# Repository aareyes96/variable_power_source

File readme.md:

# Variable Power Source

An essential tool in an electronics workshop is a Variable Power Source. This must regulate current and voltage delivered in addition to having protections against short circuits.

This Variable Power Supply is built by modifying an old PC ATX power supply and based on a tutorial made by Cuban electronics [here](http://cubaelectronica.blogspot.com/2017/06/hacer-fuente-atx-pc-variable-desde-1-28.html) where the modifications that need to be made to the PC ATX Power Supply are explained.

>### _**Here the microcontroller control board is made to achieve better control precision. It also provides a real-time current, voltage and power measurement.**_

## Features

* Complete range ( from 0V to 30V and 0A to 15A ) control with a maximum precision for a wide range.
* Fast short-circuit protection.
* Minimum modifications made to ATX Power Supply.
* Nice and clear interface.
* ~~5V (of Standby supply) for USB plug~~ (Not supported yet).
* small design (all into ATX chassis) by choice.

## What do you need ?

* Bluepill (STM32F103C8T6 microcontroller based board).
* OLED 128x64 0.96"(SSD1306 based)  ~~display or LCD 16x2 Display~~(Actually not supported).
* A rotary encoder with central Button.
* LM324 IC.
* BD139 Transistor.
* Some others common components (Resistors and Capacitors, LEDs, Connectors, a little switch, etc).

## Softwares Used

* STM32CubeIDE 1.3.0 (Firmware and Debug).
* KiCAD (Schematic and PCB).
* NI Multisim 14.0 (Simulations).

## **Important Note**

>PCB layout is made to do at home (DIY). They are not optimized to manufacture with a PCB manufacturing company like JLCPCB or others.

## Preview

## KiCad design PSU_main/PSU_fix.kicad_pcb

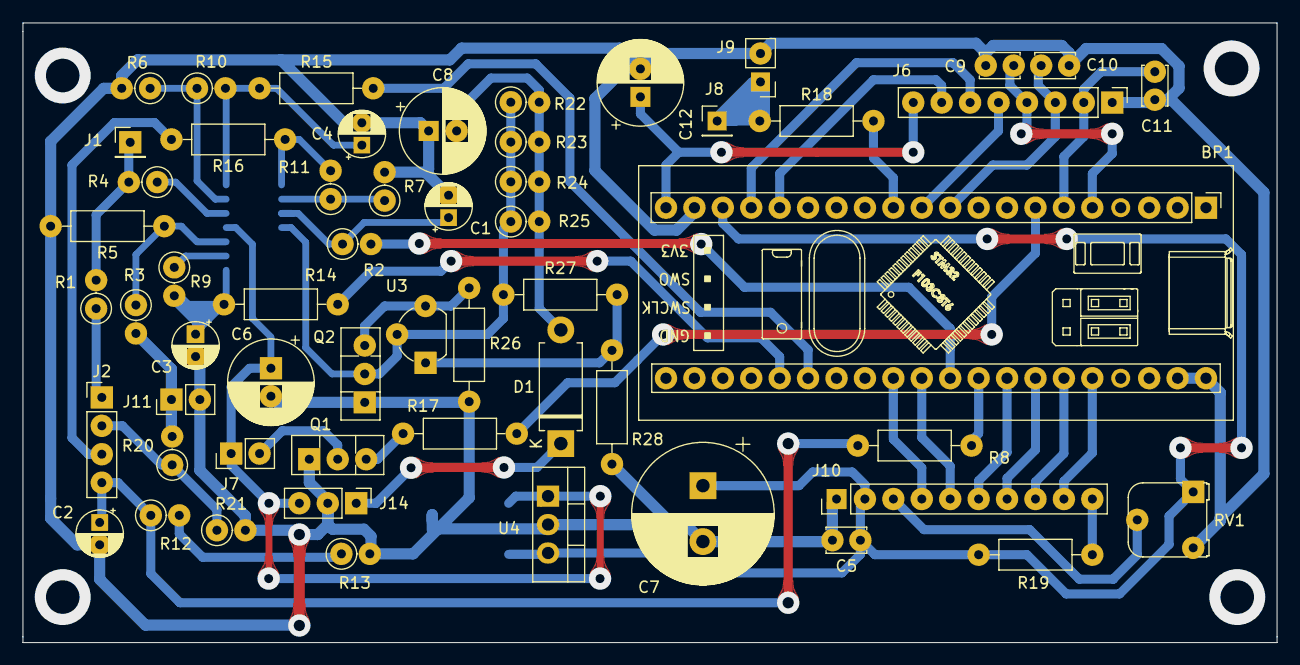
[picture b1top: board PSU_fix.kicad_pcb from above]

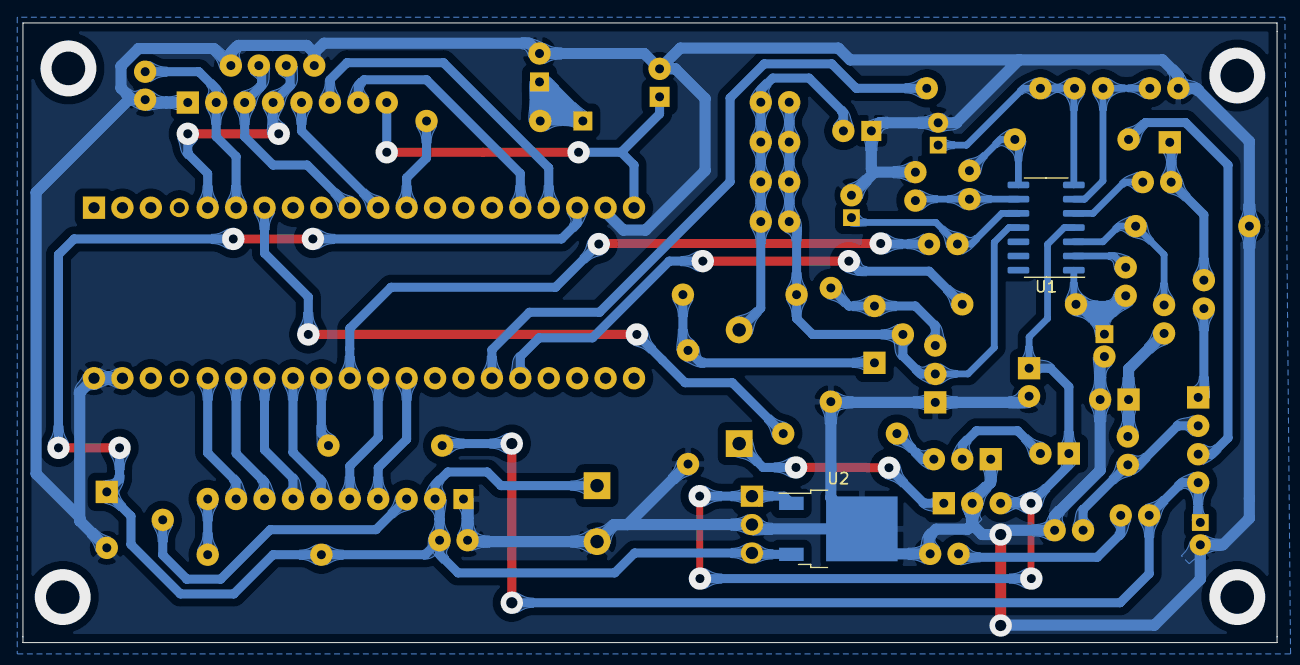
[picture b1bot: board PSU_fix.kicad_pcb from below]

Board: 2 copper layers, 112.1 x 55.4 mm, 58 parts (2 on the bottom side), 48 nets.

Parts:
BP1: BluePill_1; YAAJ_BluePill_1
C1, C2, C3, C4: 10u; CP_Radial_D4.0mm_P2.00mm
C5, C9, C10, C11: 100n; C_Disc_D3.4mm_W2.1mm_P2.50mm
C6, C8, C12: 100u; CP_Radial_D7.5mm_P2.50mm
C7: 4700u; CP_Radial_D12.5mm_P5.00mm
D1: D_Schottky; D_DO-15_P10.16mm_Horizontal
J1: RSHUNT; PinHeader_1x01_P2.54mm_Vertical
J2: TL494; PinHeader_1x04_P2.54mm_Vertical
J6: OLED; PinHeader_1x08_P2.54mm_Vertical
J7: PSU FAN; PinHeader_1x02_P2.54mm_Vertical
J8: PS_ON; PinHeader_1x01_P2.54mm_Vertical
J9: SW_STBY; PinHeader_1x02_P2.54mm_Vertical
J10: LCD 16x2; PinHeader_1x10_P2.54mm_Vertical
J11: Conn_01x02; PinHeader_1x02_P2.54mm_Vertical
J14: 12_SIMETRICOS; PinHeader_1x03_P2.54mm_Vertical
Q1: BD139; TO-126-3_Vertical
Q2: BD138; TO-126-3_Vertical
R1, R2, R4, R21: 2K; R_Axial_DIN0207_L6.3mm_D2.5mm_P2.54mm_Vertical
R3: 22k; R_Axial_DIN0207_L6.3mm_D2.5mm_P2.54mm_Vertical
R5: 2k; R_Axial_DIN0207_L6.3mm_D2.5mm_P10.16mm_Horizontal
R6, R9, R20: 10K; R_Axial_DIN0207_L6.3mm_D2.5mm_P2.54mm_Vertical
R7: 5.1K; R_Axial_DIN0207_L6.3mm_D2.5mm_P2.54mm_Vertical
R8, R16, R18: 2K; R_Axial_DIN0207_L6.3mm_D2.5mm_P10.16mm_Horizontal
R10: 20K; R_Axial_DIN0207_L6.3mm_D2.5mm_P2.54mm_Vertical
R11: 2.7K; R_Axial_DIN0207_L6.3mm_D2.5mm_P2.54mm_Vertical
R12: 220; R_Axial_DIN0207_L6.3mm_D2.5mm_P2.54mm_Vertical
R13: 150; R_Axial_DIN0207_L6.3mm_D2.5mm_P2.54mm_Vertical
R14, R15: 220; R_Axial_DIN0207_L6.3mm_D2.5mm_P10.16mm_Horizontal
R17: 1K; R_Axial_DIN0207_L6.3mm_D2.5mm_P10.16mm_Horizontal
R19: 100; R_Axial_DIN0207_L6.3mm_D2.5mm_P10.16mm_Horizontal
R22, R23, R24, R25: 4.7K; R_Axial_DIN0207_L6.3mm_D2.5mm_P2.54mm_Vertical
R26, R27: 2.2k; R_Axial_DIN0207_L6.3mm_D2.5mm_P10.16mm_Horizontal
R28: 8.2k; R_Axial_DIN0207_L6.3mm_D2.5mm_P10.16mm_Horizontal
RV1: 10K; Potentiometer_Runtron_RM-065_Vertical
U1: LM324; SOIC-14_3.9x8.7mm_P1.27mm
U2: L7805; TO-252-2
U3: TL431LP; TO-92_Wide
U4: L7805; TO-220-3_Vertical

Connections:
+5V: BP1.18, C5.1, C7.1, J10.2, R19.1, RV1.1, U2.3, U4.3
+12V: C6.1, J7.1, J14.3, U1.4, U2.1, U4.1
-12V: Q2.2, R22.1, R23.1, R24.1, R25.1, R27.1, U1.11, U3.2
/PIN_1_TL494: J2.2, R20.1, R21.1
/PIN_2_TL494: J2.3, R16.2
/PIN_15_TL494: C2.1, J2.4, R8.1, R12.1
/PIN_16_TL494: J2.1, R1.1
A0: BP1.25, R14.2
A1: BP1.26, R15.2
A6: BP1.31, R2.2
A7: BP1.32, R8.2
A10: BP1.7, R17.2
B4: BP1.12, R18.2
GND: BP1.19, BP1.39, BP1.40, C1.2, C2.2, C3.2, C4.2, C5.2, C6.2, C7.2, C8.1, C9.1, C10.2, C11.1, C12.2, J6.1, J9.2, J10.1, J11.2, J14.2, Q1.1, Q2.1, R5.2, R6.2, R7.2, R13.2, R21.2, R26.2, R28.2, RV1.3, U2.2, U4.2
unnamed: BP1.5, C9.2, J6.4
unnamed: BP1.6, C11.2, J6.2
unnamed: BP1.10, C10.1, J6.3
unnamed: BP1.11, J6.5
unnamed: BP1.16, J6.7
unnamed: BP1.17, J6.6
unnamed: BP1.20, C12.1, J6.8
unnamed: BP1.29, J10.4
unnamed: BP1.30, J10.5
unnamed: BP1.33, J10.6
unnamed: BP1.34, J10.7
unnamed: BP1.35, J10.8
unnamed: BP1.36, J10.9
unnamed: C1.1, R2.1, U1.10
unnamed: C3.1, R9.2, R14.1, U1.1
unnamed: C4.1, R10.2, R15.1, U1.7
unnamed: C8.2, D1.2, R22.2, R23.2, R24.2, R25.2
unnamed: D1.1, J14.1
unnamed: J1.1, R1.2, R4.2
unnamed: J7.2, Q1.2
unnamed: J8.1, J9.1, R18.1
unnamed: J10.3, RV1.2
unnamed: J10.10, R19.2
unnamed: Q1.3, R17.1
unnamed: Q2.3, R26.1, U3.3
unnamed: R3.1, R5.1, U1.3
unnamed: R4.1, U1.5
unnamed: R9.1, U1.2
unnamed: R6.1, R10.1, U1.6
unnamed: R7.1, R11.1, U1.9
unnamed: R11.2, R16.1, U1.8
unnamed: R12.2, R13.1
unnamed: R27.2, R28.1, U3.1
Vout: J11.1, R3.2, R20.2

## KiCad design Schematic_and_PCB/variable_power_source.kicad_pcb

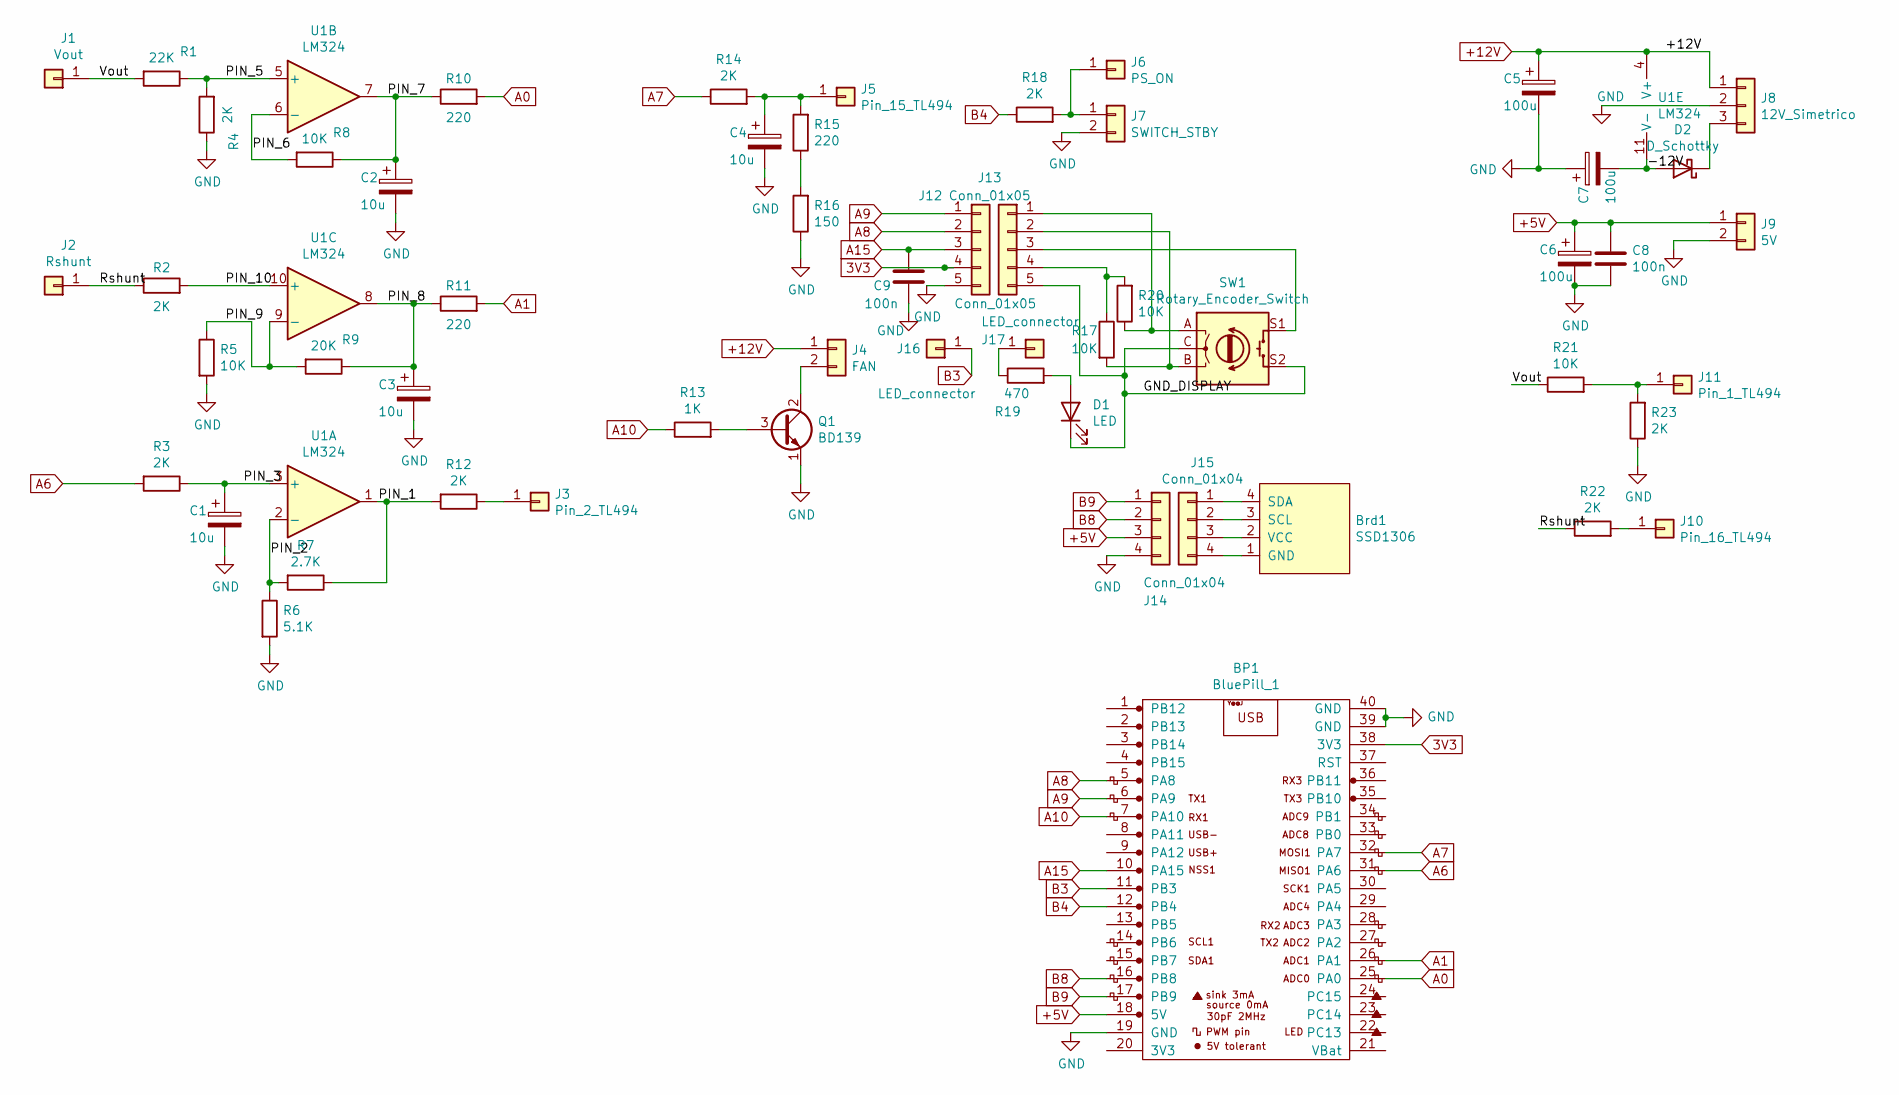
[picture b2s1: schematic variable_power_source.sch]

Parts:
BP1: BluePill_1; YAAJ_BluePill
Brd1: SSD1306; 128x64OLED
C1, C2, C3, C4: 10u; CP_Radial_D4.0mm_P2.00mm
C5, C6, C7: 100u; CP_Radial_D8.0mm_P2.50mm
C8, C9: 100n; C_Disc_D4.3mm_W1.9mm_P5.00mm
D1: LED; LED_D5.0mm
D2: D_Schottky; D_DO-41_SOD81_P10.16mm_Horizontal
J1: Vout; PinHeader_1x01_P2.54mm_Vertical
J2: Rshunt; PinHeader_1x01_P2.54mm_Vertical
J3: Pin_2_TL494; PinHeader_1x01_P2.54mm_Vertical
J4: FAN; PinHeader_1x02_P2.54mm_Vertical
J5: Pin_15_TL494; PinHeader_1x01_P2.54mm_Vertical
J6: PS_ON; PinHeader_1x01_P2.54mm_Vertical
J7: SWITCH_STBY; PinHeader_1x02_P2.54mm_Vertical
J8: 12V_Simetrico; PinHeader_1x03_P2.54mm_Vertical
J9: 5V; PinHeader_1x02_P2.54mm_Vertical
J10: Pin_16_TL494; PinHeader_1x01_P2.54mm_Vertical
J11: Pin_1_TL494; PinHeader_1x01_P2.54mm_Vertical
J12, J13: Conn_01x05; PinHeader_1x05_P2.54mm_Vertical
J14, J15: Conn_01x04; PinHeader_1x04_P2.54mm_Vertical
J16, J17: LED_connector; PinHeader_1x01_P2.54mm_Vertical
Q1: BD139; TO-126-3_Vertical
R1: 22K; R_Axial_DIN0207_L6.3mm_D2.5mm_P2.54mm_Vertical
R2, R3, R4, R12, R14, R18, R22, R23: 2K; R_Axial_DIN0207_L6.3mm_D2.5mm_P2.54mm_Vertical
R5, R8, R17, R20, R21: 10K; R_Axial_DIN0207_L6.3mm_D2.5mm_P2.54mm_Vertical
R6: 5.1K; R_Axial_DIN0207_L6.3mm_D2.5mm_P2.54mm_Vertical
R7: 2.7K; R_Axial_DIN0207_L6.3mm_D2.5mm_P2.54mm_Vertical
R9: 20K; R_Axial_DIN0207_L6.3mm_D2.5mm_P2.54mm_Vertical
R10, R11, R15: 220; R_Axial_DIN0207_L6.3mm_D2.5mm_P2.54mm_Vertical
R13: 1K; R_Axial_DIN0207_L6.3mm_D2.5mm_P2.54mm_Vertical
R16: 150; R_Axial_DIN0207_L6.3mm_D2.5mm_P2.54mm_Vertical
R19: 470; R_Axial_DIN0207_L6.3mm_D2.5mm_P2.54mm_Vertical
SW1: Rotary_Encoder_Switch; RotaryEncoder_Alps_EC11E-Switch_Vertical_H20mm_CircularMoun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
U1: LM324; SOIC-14_3.9x8.7mm_P1.27mm

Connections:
3V3: BP1.38 (3V3), J12.4
+5V: BP1.18 (5V), C6.1, C8.1, J9.1, J14.3
+12V: C5.1, J4.1, J8.1, U1.4 (V+)
/-12V: C7.2, D2.2 (A), U1.11 (V-)
/GND_DISPLAY: D1.1 (K), J13.5, SW1.C, SW1.S2
/PIN_1: R7.1, R12.2, U1.1
/PIN_2: R6.1, R7.2, U1.2 (-)
/PIN_3: C1.1, R3.1, U1.3 (+)
/PIN_5: R1.1, R4.2, U1.5 (+)
/PIN_6: R8.2, U1.6 (-)
/PIN_7: C2.1, R8.1, R10.1, U1.7
/PIN_8: C3.1, R9.1, R11.1, U1.8
/PIN_9: R5.1, R9.2, U1.9 (-)
/PIN_10: R2.2, U1.10 (+)
/Rshunt: J2.1, R2.1, R22.1
/Vout: J1.1, R1.2, R21.1
A0: BP1.25 (PA0), R10.2
A1: BP1.26 (PA1), R11.2
A6: BP1.31 (PA6), R3.2
A7: BP1.32 (PA7), R14.1
A8: BP1.5 (PA8), J12.2
A9: BP1.6 (PA9), J12.1
A10: BP1.7 (PA10), R13.1
A15: BP1.10 (PA15), C9.1, J12.3
B3: BP1.11 (PB3), J16.1
B4: BP1.12 (PB4), R18.1
B8: BP1.16 (PB8), J14.2
B9: BP1.17 (PB9), J14.1
GND: BP1.19 (GND), BP1.39 (GND), BP1.40 (GND), C1.2, C2.2, C3.2, C4.2, C5.2, C6.2, C7.1, C8.2, C9.2, J7.2, J8.2, J9.2, J12.5, J14.4, Q1.1 (E), R4.1, R5.2, R6.2, R16.1, R23.1
unnamed: Brd1.1 (GND), J15.4
unnamed: Brd1.2 (VCC), J15.3
unnamed: Brd1.3 (SCL), J15.2
unnamed: Brd1.4 (SDA), J15.1
unnamed: C4.1, J5.1, R14.2, R15.2
unnamed: D1.2 (A), R19.2
unnamed: D2.1 (K), J8.3
unnamed: J3.1, R12.1
unnamed: J4.2, Q1.2 (C)
unnamed: J6.1, J7.1, R18.2
unnamed: J10.1, R22.2
unnamed: J11.1, R21.2, R23.2
unnamed: J13.1, R20.1, SW1.A
unnamed: J13.2, R17.2, SW1.B
unnamed: J13.3, SW1.S1
unnamed: J13.4, R17.1, R20.2
unnamed: J17.1, R19.1
unnamed: Q1.3 (B), R13.2
unnamed: R15.1, R16.2

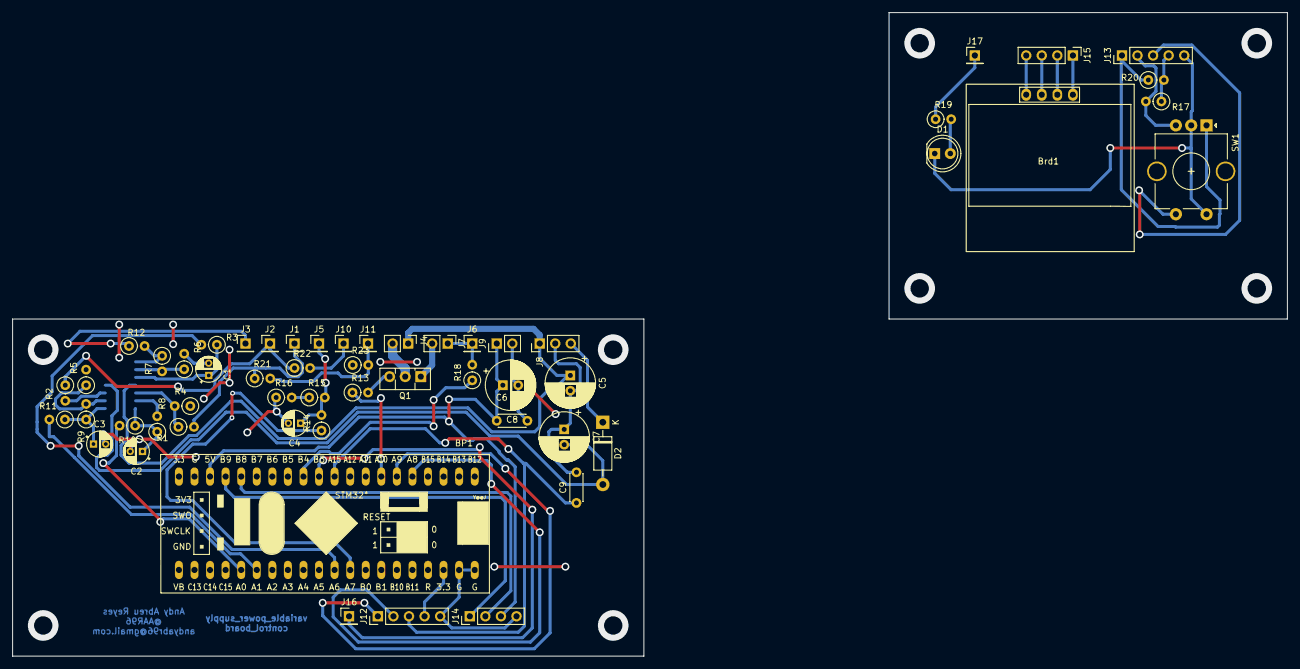
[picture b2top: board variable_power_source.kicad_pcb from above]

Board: 2 copper layers, 103.0 x 55.0 mm, 56 parts (1 on the bottom side), 48 nets.

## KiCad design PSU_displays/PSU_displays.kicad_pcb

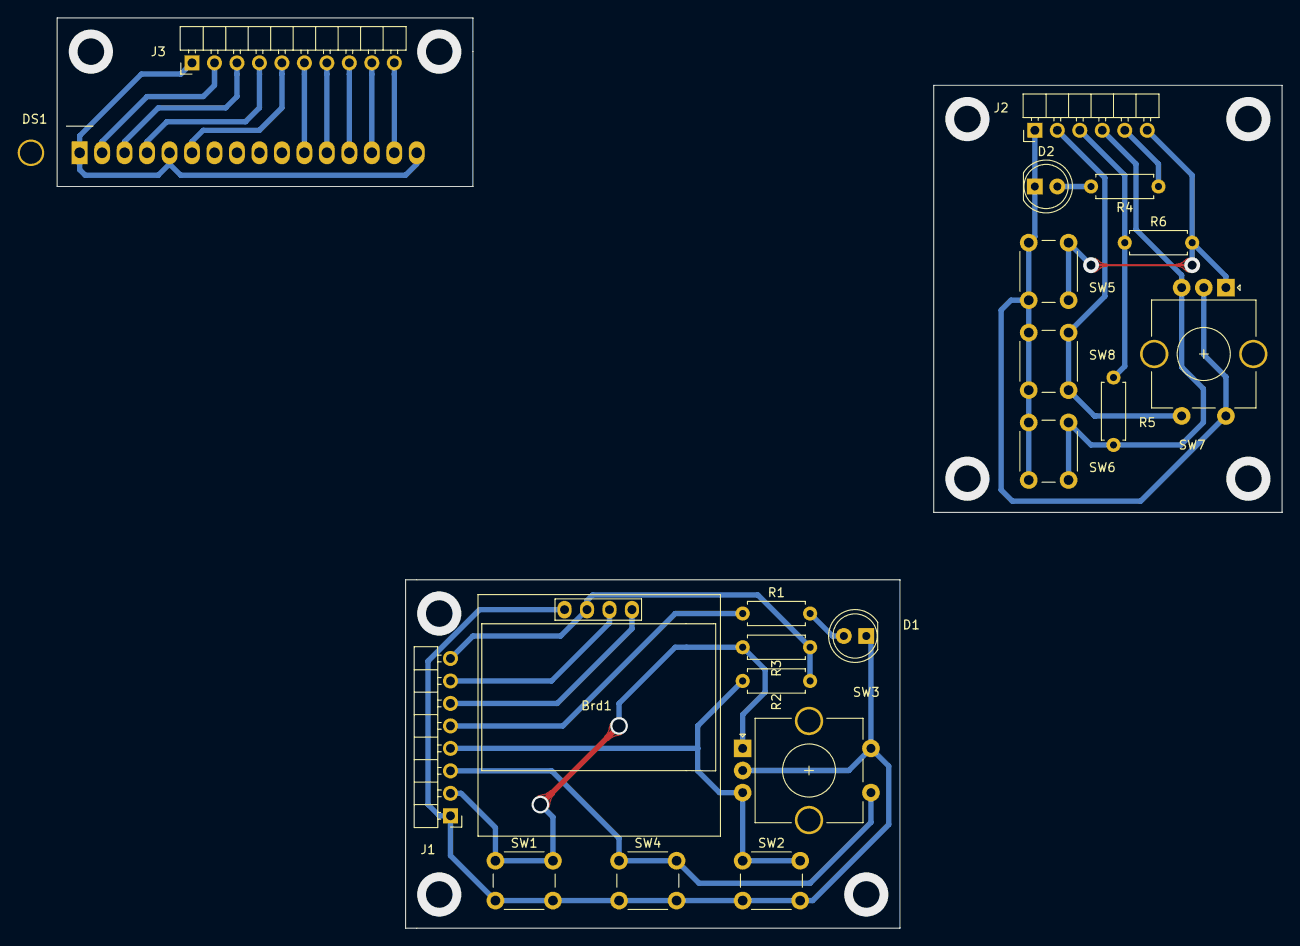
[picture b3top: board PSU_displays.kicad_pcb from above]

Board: 2 copper layers, 138.4 x 102.9 mm, 21 parts (0 on the bottom side), 26 nets.

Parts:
Brd1: SSD1306; 128x64OLED
D1, D2: LED; LED_D5.0mm
DS1: WC1602A
J1: Conn_01x08; PinHeader_1x08_P2.54mm_Horizontal
J2: Conn_01x06; PinHeader_1x06_P2.54mm_Horizontal
J3: Conn_01x10; PinHeader_1x10_P2.54mm_Horizontal
R1, R4: 470; R_Axial_DIN0207_L6.3mm_D2.5mm_P7.62mm_Horizontal
R2, R3, R5, R6: 10K; R_Axial_DIN0207_L6.3mm_D2.5mm_P7.62mm_Horizontal
SW1, SW5: SW_A; SW_PUSH_6mm
SW2, SW6: SW_B; SW_PUSH_6mm
SW3, SW7: Rotary_Encoder_Switch; RotaryEncoder_Alps_EC11E-Switch_Vertical_H20mm_CircularMoun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
SW4, SW8: SW_ENTER; SW_PUSH_6mm

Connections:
unnamed: Brd1.1, D1.1, J1.1, SW1.2, SW2.2, SW3.C, SW3.S2, SW4.2
unnamed: Brd1.2, J1.8, R2.1, R3.1
unnamed: Brd1.3, J1.7
unnamed: Brd1.4, J1.6
unnamed: D1.2, R1.2
unnamed: D2.1, J2.1, SW5.2, SW6.2, SW7.C, SW7.S2, SW8.2
unnamed: D2.2, R4.2
unnamed: DS1.1, DS1.5, DS1.16, J3.1
unnamed: DS1.2, J3.2
unnamed: DS1.3, J3.3
unnamed: DS1.4, J3.4
unnamed: DS1.6, J3.5
unnamed: DS1.11, J3.6
unnamed: DS1.12, J3.7
unnamed: DS1.13, J3.8
unnamed: DS1.14, J3.9
unnamed: DS1.15, J3.10
unnamed: J1.2, R3.2, SW1.1, SW3.A
unnamed: J1.3, SW3.S1, SW4.1
unnamed: J1.4, R2.2, SW2.1, SW3.B
unnamed: J1.5, R1.1
unnamed: J2.2, SW7.S1, SW8.1
unnamed: J2.3, R5.1, R6.1
unnamed: J2.4, R5.2, SW6.1, SW7.B
unnamed: J2.5, R4.1
unnamed: J2.6, R6.2, SW5.1, SW7.A

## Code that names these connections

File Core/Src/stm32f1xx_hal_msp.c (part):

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  
    __HAL_RCC_GPIOA_CLK_ENABLE();
    /**ADC1 GPIO Configuration    
    PA0-WKUP     ------> ADC1_IN0
    PA1     ------> ADC1_IN1
    PA2     ------> ADC1_IN2
    PA3     ------> ADC1_IN3 
    */
    GPIO_InitStruct.Pin = GPIO_PIN_0|GPIO_PIN_1|GPIO_PIN_2|GPIO_PIN_3;
    GPIO_InitStruct.Mode = GPIO_MODE_ANALOG;
    HAL_GPIO_Init(GPIOA, &GPIO_InitStruct);

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    __HAL_RCC_ADC1_CLK_DISABLE();
  
    /**ADC1 GPIO Configuration    
    PA0-WKUP     ------> ADC1_IN0
    PA1     ------> ADC1_IN1
    PA2     ------> ADC1_IN2
    PA3     ------> ADC1_IN3 
    */
    HAL_GPIO_DeInit(GPIOA, GPIO_PIN_0|GPIO_PIN_1|GPIO_PIN_2|GPIO_PIN_3);

    /* ADC1 DMA DeInit */
    HAL_DMA_DeInit(hadc->DMA_Handle);
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  
    __HAL_RCC_GPIOB_CLK_ENABLE();
    /**I2C1 GPIO Configuration    
    PB8     ------> I2C1_SCL
    PB9     ------> I2C1_SDA 
    */
    GPIO_InitStruct.Pin = GPIO_PIN_8|GPIO_PIN_9;
    GPIO_InitStruct.Mode = GPIO_MODE_AF_OD;
    GPIO_InitStruct.Speed = GPIO_SPEED_FREQ_HIGH;
    HAL_GPIO_Init(GPIOB, &GPIO_InitStruct);
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    __HAL_RCC_I2C1_CLK_DISABLE();
  
    /**I2C1 GPIO Configuration    
    PB8     ------> I2C1_SCL
    PB9     ------> I2C1_SDA 
    */
    HAL_GPIO_DeInit(GPIOB, GPIO_PIN_8|GPIO_PIN_9);

  /* USER CODE BEGIN I2C1_MspDeInit 1 */

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  
    __HAL_RCC_GPIOA_CLK_ENABLE();
    /**TIM1 GPIO Configuration    
    PA8     ------> TIM1_CH1
    PA9     ------> TIM1_CH2 
    */
    GPIO_InitStruct.Pin = GPIO_PIN_8|GPIO_PIN_9;
    GPIO_InitStruct.Mode = GPIO_MODE_INPUT;
    GPIO_InitStruct.Pull = GPIO_NOPULL;
    HAL_GPIO_Init(GPIOA, &GPIO_InitStruct);
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  
    __HAL_RCC_GPIOA_CLK_ENABLE();
    /**TIM3 GPIO Configuration    
    PA6     ------> TIM3_CH1
    PA7     ------> TIM3_CH2 
    */
    GPIO_InitStruct.Pin = GPIO_PIN_6|GPIO_PIN_7;
    GPIO_InitStruct.Mode = GPIO_MODE_AF_PP;
    GPIO_InitStruct.Speed = GPIO_SPEED_FREQ_LOW;
    HAL_GPIO_Init(GPIOA, &GPIO_InitStruct);
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    __HAL_RCC_TIM1_CLK_DISABLE();
  
    /**TIM1 GPIO Configuration    
    PA8     ------> TIM1_CH1
    PA9     ------> TIM1_CH2 
    */
    HAL_GPIO_DeInit(GPIOA, GPIO_PIN_8|GPIO_PIN_9);

    /* TIM1 interrupt DeInit */
    HAL_NVIC_DisableIRQ(TIM1_BRK_IRQn);
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
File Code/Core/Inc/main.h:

/* USER CODE BEGIN Header */
/**
  ******************************************************************************
  * @file           : main.h
  * @brief          : Header for main.c file.
  *                   This file contains the common defines of the application.
  ******************************************************************************
  * @attention
  *
  * <h2><center>&copy; Copyright (c) 2021 STMicroelectronics.
  * All rights reserved.</center></h2>
  *
  * This software component is licensed by ST under BSD 3-Clause license,
  * the "License"; You may not use this file except in compliance with the
  * License. You may obtain a copy of the License at:
  *                        opensource.org/licenses/BSD-3-Clause
  *
  ******************************************************************************
  */
/* USER CODE END Header */

/* Define to prevent recursive inclusion -------------------------------------*/
#ifndef __MAIN_H
#define __MAIN_H

#ifdef __cplusplus
extern "C" {
#endif

/* Includes ------------------------------------------------------------------*/
#include "stm32f1xx_hal.h"

/* Private includes ----------------------------------------------------------*/
/* USER CODE BEGIN Includes */

/* USER CODE END Includes */

/* Exported types ------------------------------------------------------------*/
/* USER CODE BEGIN ET */

/* USER CODE END ET */

/* Exported constants --------------------------------------------------------*/
/* USER CODE BEGIN EC */

/* USER CODE END EC */

/* Exported macro ------------------------------------------------------------*/
/* USER CODE BEGIN EM */

/* USER CODE END EM */

void HAL_TIM_MspPostInit(TIM_HandleTypeDef *htim);

/* Exported functions prototypes ---------------------------------------------*/
void Error_Handler(void);

/* USER CODE BEGIN EFP */

/* USER CODE END EFP */

/* Private defines -----------------------------------------------------------*/
#define LCD_RS_Pin GPIO_PIN_4
#define LCD_RS_GPIO_Port GPIOA
#define LCD_E_Pin GPIO_PIN_5
#define LCD_E_GPIO_Port GPIOA
#define LCD_D4_Pin GPIO_PIN_0
#define LCD_D4_GPIO_Port GPIOB
#define LCD_D5_Pin GPIO_PIN_1
#define LCD_D5_GPIO_Port GPIOB
#define LCD_D6_Pin GPIO_PIN_10
#define LCD_D6_GPIO_Port GPIOB
#define LCD_D7_Pin GPIO_PIN_11
#define LCD_D7_GPIO_Port GPIOB
#define FAN_Pin GPIO_PIN_10
#define FAN_GPIO_Port GPIOA
#define Button_Pin GPIO_PIN_15
#define Button_GPIO_Port GPIOA
#define Button_EXTI_IRQn EXTI15_10_IRQn
#define LED_Pin GPIO_PIN_3
#define LED_GPIO_Port GPIOB
/* USER CODE BEGIN Private defines */

/* USER CODE END Private defines */

#ifdef __cplusplus
}
#endif

#endif /* __MAIN_H */

/************************ (C) COPYRIGHT STMicroelectronics *****END OF FILE****/

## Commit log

2021-05-03 fix pcb errors and add identity mask
2021-05-03 relocate and short files
2021-05-03 add readme
2021-09-18 updates and fixes
2021-09-19 fix some things
2021-09-19 updae readme
2021-09-19 photo update
2021-09-24 add better preview photos
